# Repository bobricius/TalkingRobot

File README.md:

simple children toy robot 

Features 

- max. 44khz, 16bit wav 
- supply voltage 3,3V to 5V can be powered with LIR2032 battery, not CR2032! 
- you can optionally solder mini or micro usb connector 
- dimensions 5 cm x 10 cm 
- upgradeable firmware, AVR AtTiny861 based board 
- 16bit output created from 2 shifted 8bit PWM channels, good quality 
- output for speraker 
- can driving small speaker, amplifier is recommended 
- 8 control signals on header active in low 
- 8 buttons for testing + 2 LED on eyes, 1 LED as heart button (reset) + 8 LED connected to buttons 
- micro SD card push-push connector 

https://www.youtube.com/watch?v=AGjfrQgZr3E

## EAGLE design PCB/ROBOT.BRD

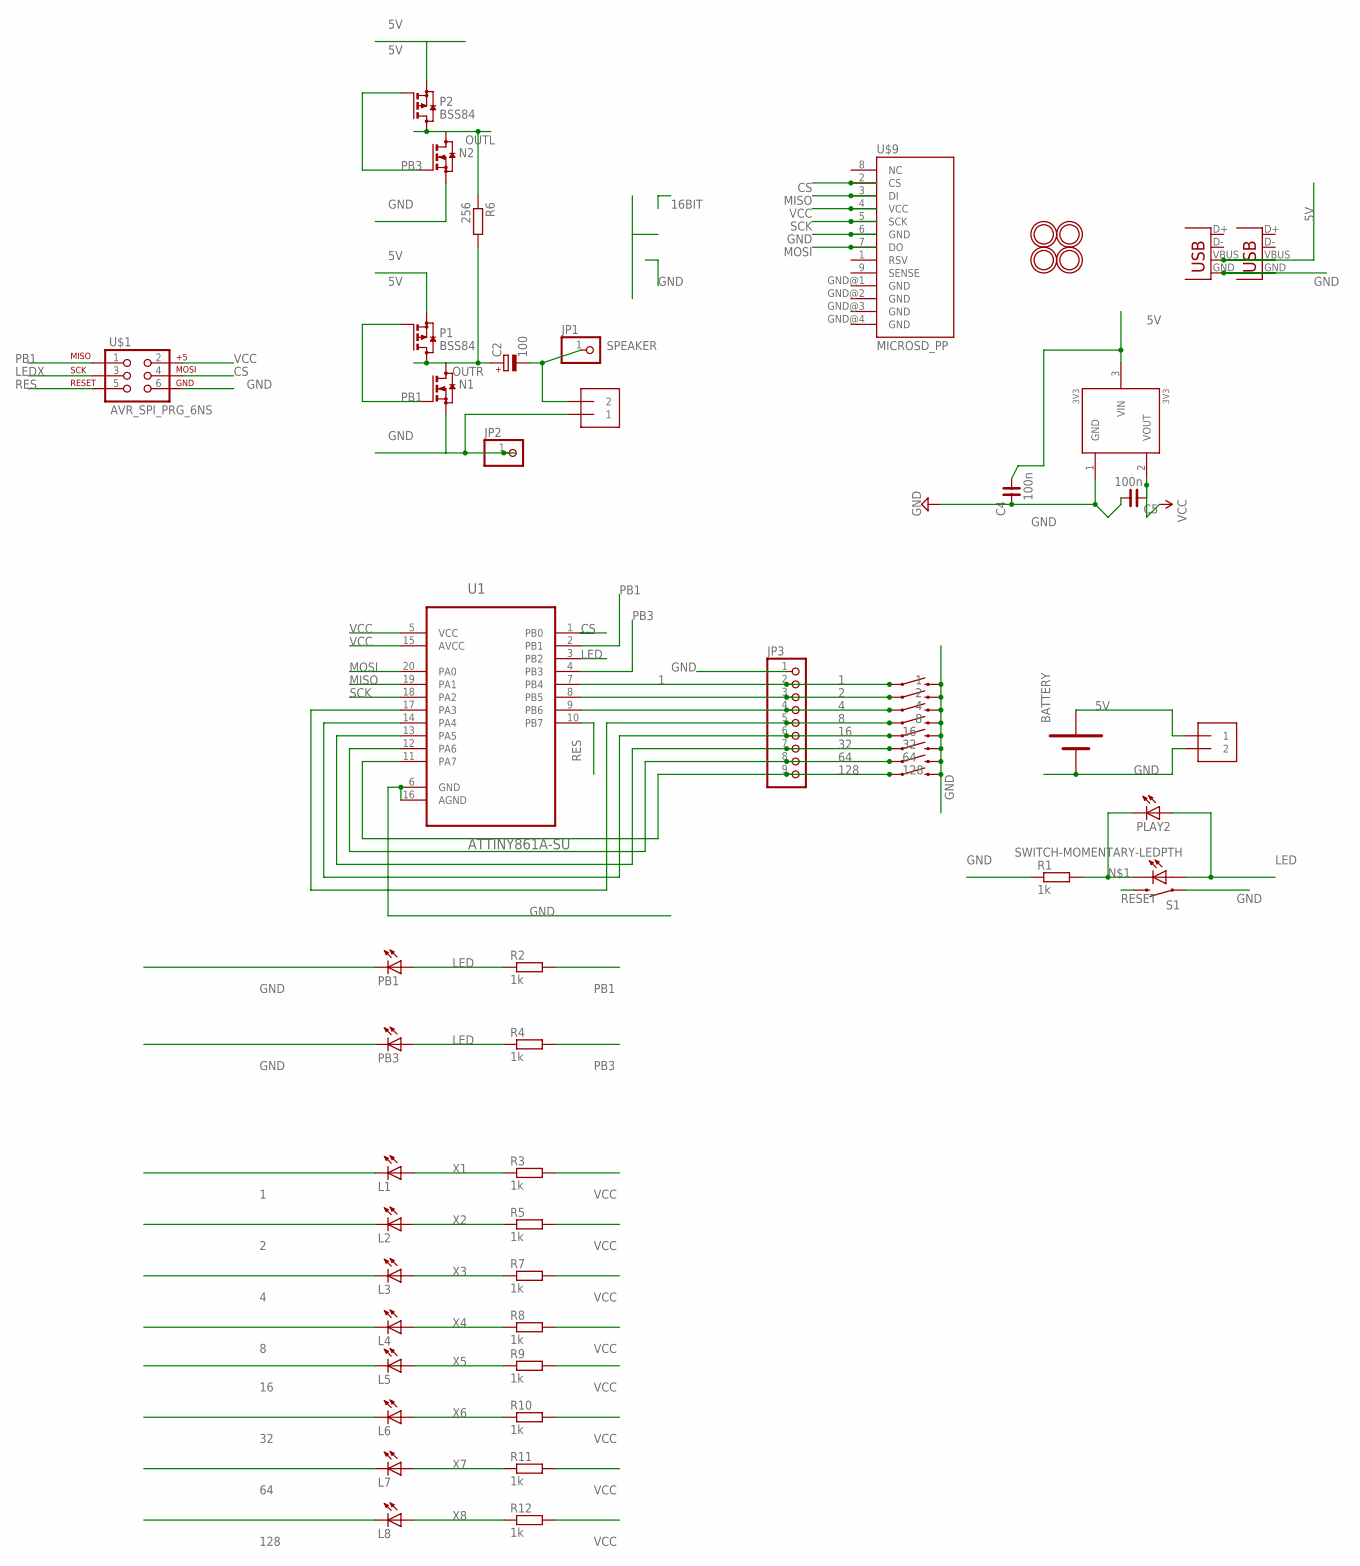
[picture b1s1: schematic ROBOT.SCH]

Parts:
1, 2, 4, 8, 16, 32, 64, 128: SWITCH-MOMENTARY-2-SMD-1101NE; TACTILE-SWITCH-1101NE
3V3: 3V3; SOT23
BATTERY: BATTERY-1XAA20MM; BATTCOM_20MM_PTH
C2: 100; 153CLV-0605
C4, C5: 100n; C0603
J1, J2: 1X2-3.5MM
JP1, JP2: PINHD-1X1; 1X01
JP3: PINHD-1X9; 1X09
L1, L2, L3, L4, L5, L6, L7, L8: LEDSML0603; SML0603
N1, N2: BSS123; SOT23
P1, P2: BSS84; SOT23
PB1, PB3: LEDSML0603; SML0603
PLAY2: LEDSML0603; SML0603
R1, R2, R3, R4, R5, R7, R8, R9, R10, R11, R12: 1k; R0603
R6: 256; R0603
S1: SWITCH-MOMENTARY-LEDPTH; TACTILE-PTH-LED-12MM
U1: ATTINY861A-SU; SOIC127P1032X265-20N
U$1: AVR_SPI_PRG_6NS; 2X3-NS
U$3, U$4: MOUNTINGHOLE1.0; MOUNTINGHOLE_1.0_PLATED
U$6, U$7: MOUNTINGHOLE3.0THIN; MOUNTINGHOLE_3.0_PLATEDTHIN
U$9: MICROSD_PP
X1: USB-MICROB
X5: USBSMD; USB-MINIB

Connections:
1: 1.P$1 (1), JP3.2, L1.C, U1.7 (PB4)
2: 2.P$1 (1), JP3.3, L2.C, U1.8 (PB5)
4: 4.P$1 (1), JP3.4, L3.C, U1.9 (PB6)
5V: 3V3.3 (VIN), BATTERY.+, C4.1, J2.1, P1.2 (S), P2.2 (S), X1.VBUS, X5.VBUS
8: 8.P$1 (1), JP3.5, L4.C, U1.17 (PA3)
16: 16.P$1 (1), JP3.6, L5.C, U1.14 (PA4)
32: 32.P$1 (1), JP3.7, L6.C, U1.13 (PA5)
64: 64.P$1 (1), JP3.8, L7.C, U1.12 (PA6)
128: 128.P$1 (1), JP3.9, L8.C, U1.11 (PA7)
CS: U1.1 (PB0), U$1.4, U$9.2 (CS)
GND: 1.P$2 (2), 2.P$2 (2), 3V3.1 (GND), 4.P$2 (2), 8.P$2 (2), 16.P$2 (2), 32.P$2 (2), 64.P$2 (2), 128.P$2 (2), BATTERY.-, C4.2, C5.1, J1.1, J2.2, JP2.1, JP3.1, N1.2 (S), N2.2 (S), PB1.C, PB3.C, R1.1, S1.4 (1), U1.6 (GND), U1.16 (AGND), U$1.6, U$9.6 (GND), X1.GND, X5.GND
LED: PB1.A, PB3.A, PLAY2.A, R2.1, R4.1, S1.A, U1.3 (PB2)
LEDX: U$1.3
MISO: U1.19 (PA1), U$9.3 (DI)
MOSI: U1.20 (PA0), U$9.7 (DO)
unnamed: PLAY2.C, R1.2, S1.C
OUTL: N2.3 (D), P2.3 (D), R6.1
OUTR: C2.+, N1.3 (D), P1.3 (D), R6.2
PB1: N1.1 (G), P1.1 (G), R2.2, U1.2 (PB1), U$1.1
PB3: N2.1 (G), P2.1 (G), R4.2, U1.4 (PB3)
RES: U1.10 (PB7), U$1.5
RESET: S1.2
SCK: U1.18 (PA2), U$9.5 (SCK)
SPEAKER: C2.-, J1.2, JP1.1
VCC: 3V3.2 (VOUT), C5.2, R3.2, R5.2, R7.2, R8.2, R9.2, R10.2, R11.2, R12.2, U1.5 (VCC), U1.15 (AVCC), U$1.2, U$9.4 (VCC)
X1: L1.A, R3.1
X2: L2.A, R5.1
X3: L3.A, R7.1
X4: L4.A, R8.1
X5: L5.A, R9.1
X6: L6.A, R10.1
X7: L7.A, R11.1
X8: L8.A, R12.1

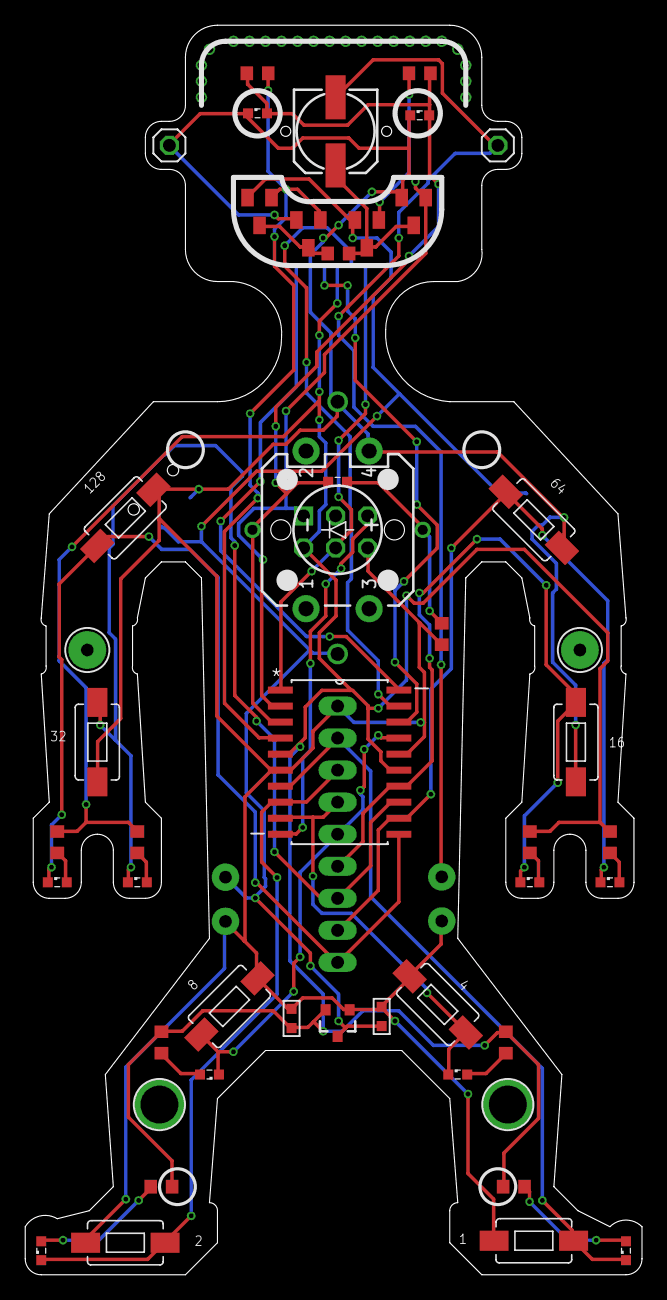
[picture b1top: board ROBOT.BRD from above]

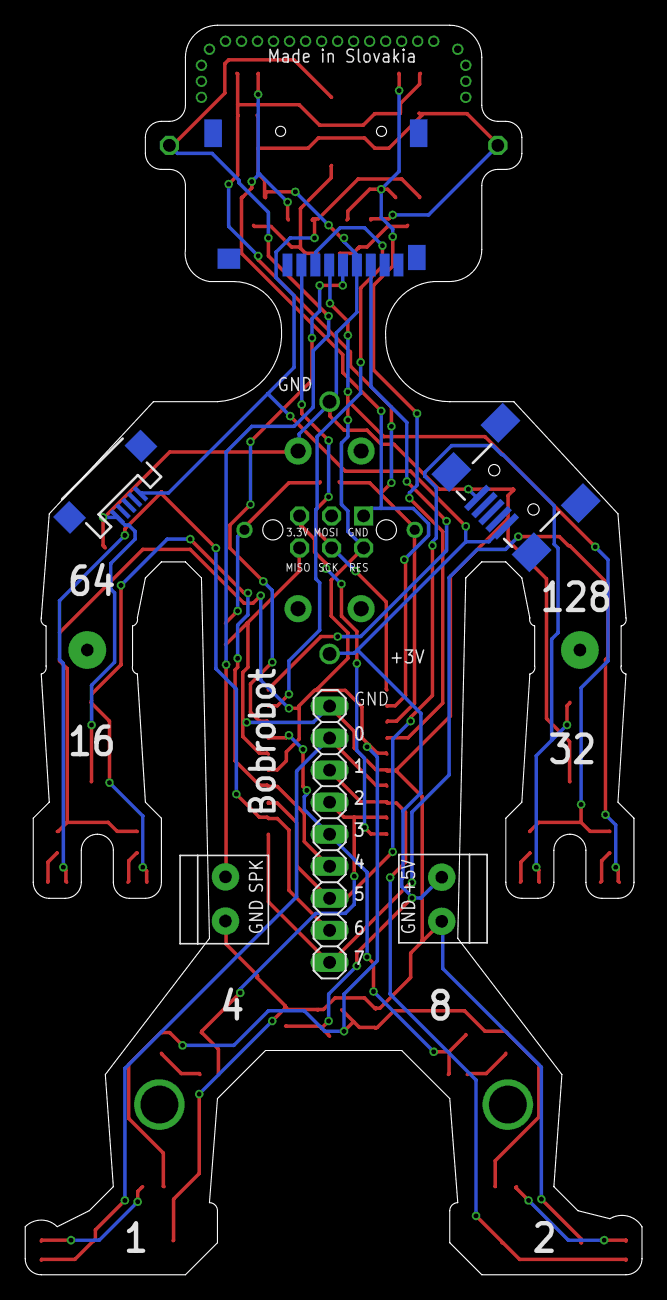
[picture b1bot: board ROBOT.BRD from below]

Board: 2 copper layers, 48.9 x 99.1 mm, 55 parts (7 on the bottom side), 31 nets.

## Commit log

2017-02-02 :octocat: Added .gitattributes & .gitignore files
2017-02-02 Upload
2017-02-02 PCB updated to rev2.
